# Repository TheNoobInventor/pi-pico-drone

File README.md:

# Raspberry pi pico drone

A micro drone is made using the Raspberry Pi Pico W. It is fitted with the MPU6050 IMU module and BMP280 barometric sensor. The drone will be controlled using TinyMPC and employ a Micro-ROS client on FreeRTOS.

🚧	***(Work in Progress)*** 

## Bill of Materials

The following components were used in this project:

| Part | Quantity |
| :-- | :-- |
| Raspberry Pi Pico W | 1 |
| MPU6050 module | 1 |
| BMP280 module | 1 |
| 1S 500mAh Lipo Battery| 1 |
| 1020 Coreless Motor | 4 |
| 66mm propeller (2 pairs of CW and 2 pairs of CCW) | 4  |
| XH2.54 2p connector pairs (for motors and battery) | 5 |
| si2302 N channel Mosfet| 4 |
| 1N4148 Diode | 5 |
| 100 ohm resistor | 3 |
| 300 ohm resistor | 1 |
| 1k ohm resistor | 1 |
| 10k ohm resistor | 4 |
| Female Pin headers | 40 |
| Push Button | 1 |
| LEDs | 3 |
| 1S Lipo charger | 1 |

*CW - Clockwise and CCW - Counter clockwise*

Some tools/parts used int he project are as follows:

| | Tool/Part |
| --| --|
|1| Soldering iron|
|2| 3D printer|
|3| Hot air gun|
|4| Crimping tool|
|4| Solder paste |

## Project Assembly and Wiring

The PCB was made with KiCAD and the project files are available in the [pcb directory](./hardware/pcb/).

The insides of one of the female headers had to be filed to enable the MPU6050 module be soldered and positioned horizontally to the pcb.

3D printed frame courtesy of this [thingiverse project](https://www.thingiverse.com/thing:4799075).

## Software installation
FreeRTOS
MicroROS
TinyMPC

TODO:
- Credit Anish Natekar's work
- Add component links
- Note on LED designations

# Acknowledgement
- [PicoW_Copter](https://github.com/anish-natekar/PicoW_Copter)
- [TinyMPC](https://github.com/TinyMPC/TinyMPC)

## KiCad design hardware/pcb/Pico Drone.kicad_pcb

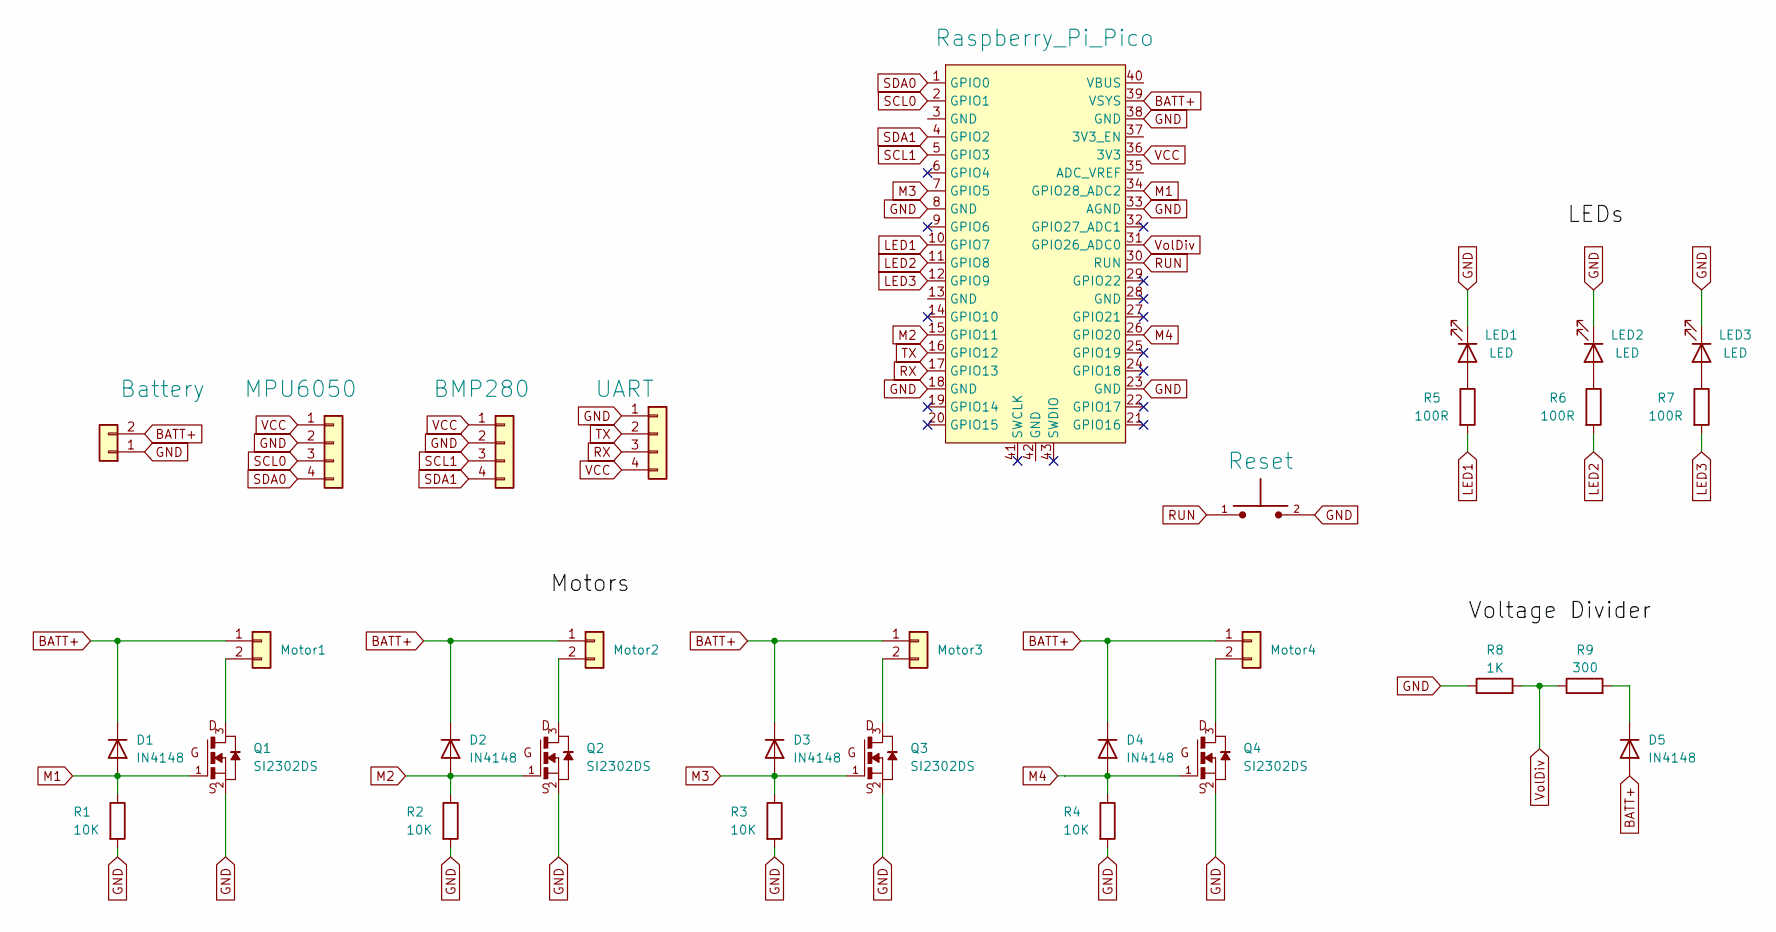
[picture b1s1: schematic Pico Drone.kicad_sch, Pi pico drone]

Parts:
Battery: Conn_01x02; PinHeader_1x02_P2.54mm_Vertical
D1, D2, D3, D4, D5: IN4148; Diode_DO-35
J1: MPU6050; PinHeader_1x04_P2.54mm_Vertical
J2: BMP280; PinHeader_1x04_P2.54mm_Vertical
J3: UART; PinHeader_1x04_P2.54mm_Vertical
LED1, LED2, LED3: LED; PinHeader_1x02_P2.54mm_Vertical
Motor1, Motor2, Motor3, Motor4: Conn_01x02; PinHeader_1x02_P2.54mm_Vertical
Q1, Q2, Q3, Q4: SI2302DS; SI2302
R1, R2, R3, R4: 10K; R_Axial_DIN0207_L6.3mm_D2.5mm_P7.62mm_Horizontal
R5, R6, R7: 100R; R_Axial_DIN0207_L6.3mm_D2.5mm_P7.62mm_Horizontal
R8: 1K; R_Axial_DIN0207_L6.3mm_D2.5mm_P7.62mm_Horizontal
R9: 300; R_Axial_DIN0207_L6.3mm_D2.5mm_P7.62mm_Horizontal
S1: Reset; smt_tactile_switch; PARTREV 1.0
U1: Raspberry_Pi_Pico

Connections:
BATT+: Battery.2, D1.1 (K), D2.1 (K), D3.1 (K), D4.1 (K), D5.2 (A), Motor1.1, Motor2.1, Motor3.1, Motor4.1, U1.39 (VSYS); also elsewhere on the board
GND: Battery.1, J1.2, J2.2, J3.1, LED1.1 (K), LED2.1 (K), LED3.1 (K), Q1.2, Q2.2, Q3.2, Q4.2, R1.2, R2.2, R3.2, R4.2, R8.1, S1.2, U1.8 (GND), U1.18 (GND), U1.23 (GND), U1.33 (AGND), U1.38 (GND); also elsewhere on the board
LED1: R5.2, U1.10 (GPIO7)
LED2: R6.2, U1.11 (GPIO8)
LED3: R7.2, U1.12 (GPIO9)
M1: D1.2 (A), Q1.1, R1.1, U1.34 (GPIO28_ADC2)
M2: D2.2 (A), Q2.1, R2.1, U1.15 (GPIO11)
M3: D3.2 (A), Q3.1, R3.1, U1.7 (GPIO5)
M4: D4.2 (A), Q4.1, R4.1, U1.26 (GPIO20)
unnamed: D5.1 (K), R9.2
unnamed: LED1.2 (A), R5.1
unnamed: LED2.2 (A), R6.1
unnamed: LED3.2 (A), R7.1
unnamed: Motor1.2, Q1.3
unnamed: Motor2.2, Q2.3
unnamed: Motor3.2, Q3.3
unnamed: Motor4.2, Q4.3
RUN: S1.1, U1.30 (RUN)
RX: J3.3, U1.17 (GPIO13)
SCL0: J1.3, U1.2 (GPIO1)
SCL1: J2.3, U1.5 (GPIO3)
SDA0: J1.4, U1.1 (GPIO0)
SDA1: J2.4, U1.4 (GPIO2)
TX: J3.2, U1.16 (GPIO12)
VCC: J1.1, J2.1, J3.4, U1.36 (3V3)
VolDiv: R8.2, R9.1, U1.31 (GPIO26_ADC0)

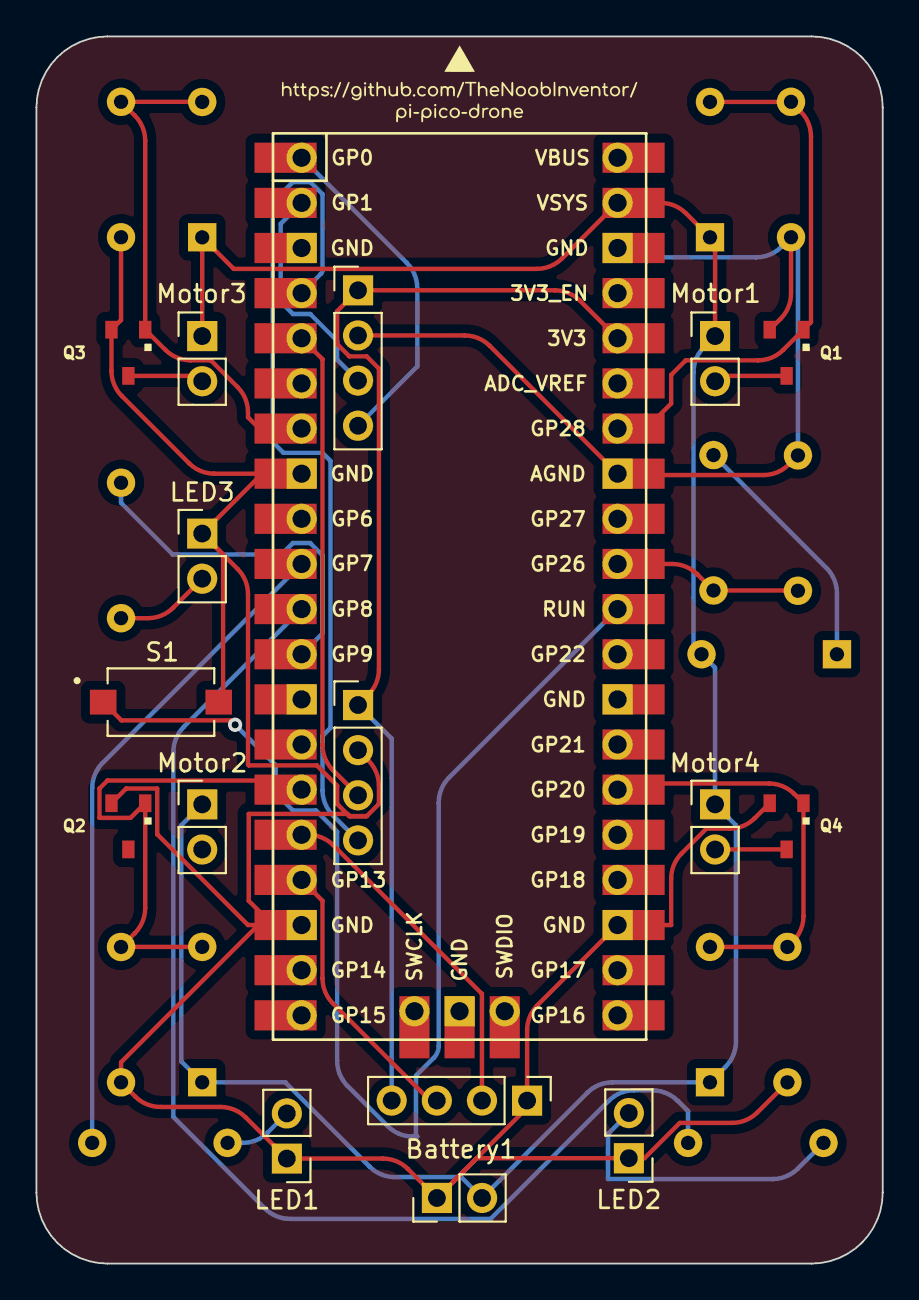
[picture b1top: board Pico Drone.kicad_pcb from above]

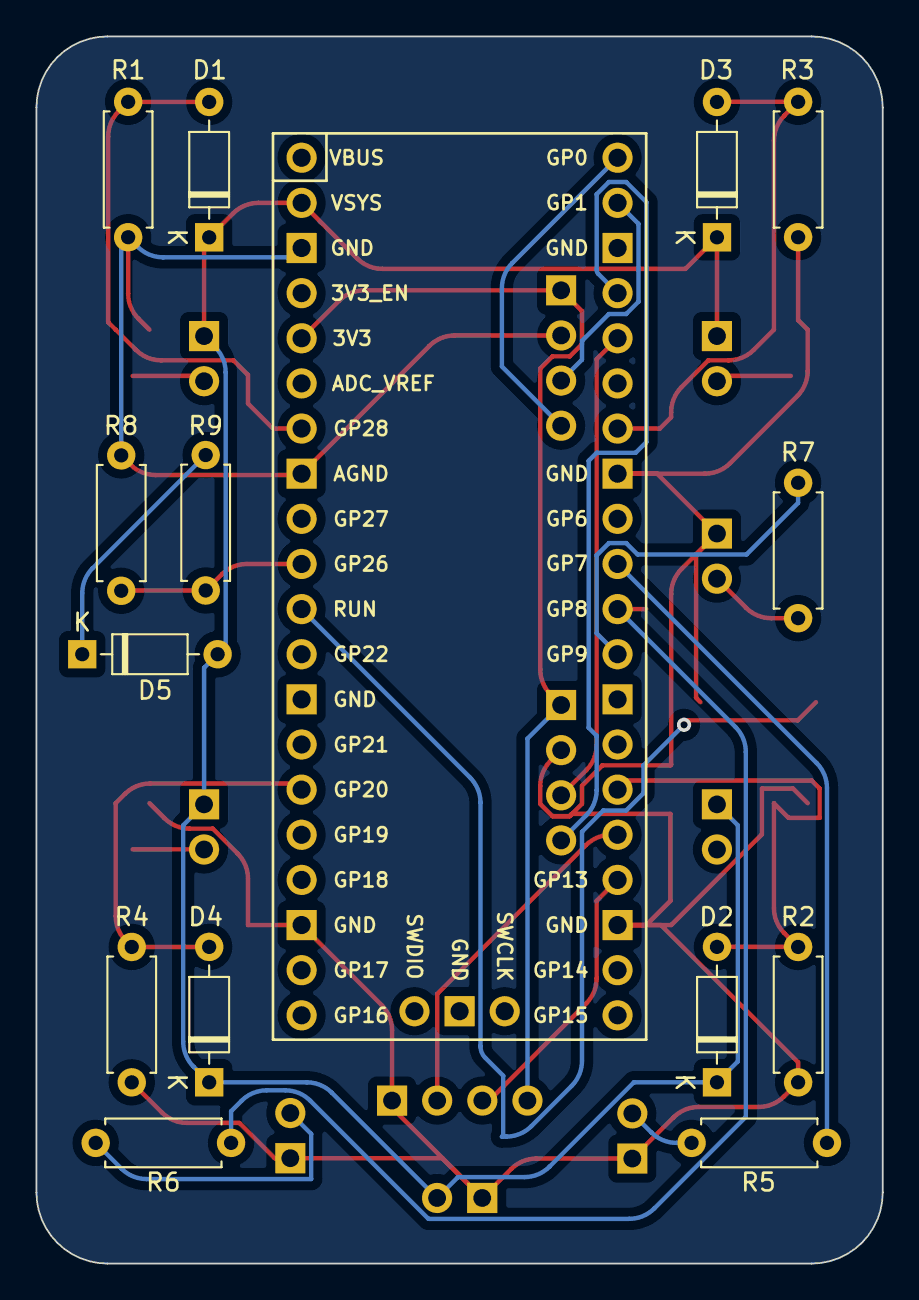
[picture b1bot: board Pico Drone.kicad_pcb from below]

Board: 2 copper layers, 47.6 x 69.1 mm, 31 parts (14 on the bottom side), 26 nets.

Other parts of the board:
Battery1: Conn_01x02; PinHeader_1x02_P2.54mm_Vertical

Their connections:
BATT+: Battery1.2; also elsewhere on the board
GND: Battery1.1; also elsewhere on the board

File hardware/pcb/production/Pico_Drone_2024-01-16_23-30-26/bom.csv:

Designator,Footprint,Quantity,Value,LCSC Part #
"Battery1, Motor1, Motor2, Motor3, Motor4",PinHeader_1x02_P2.54mm_Vertical,5,Conn_01x02,
"D1, D2, D3, D4, D5",Diode_DO-35,5,IN4148,
J1,PinHeader_1x04_P2.54mm_Vertical,1,MPU6050,
J2,PinHeader_1x04_P2.54mm_Vertical,1,BMP280,
J3,PinHeader_1x04_P2.54mm_Vertical,1,UART,
"LED1, LED2, LED3",PinHeader_1x02_P2.54mm_Vertical,3,LED,
"Q1, Q2, Q3, Q4",SI2302,4,SI2302DS,
"R1, R2, R3, R4",R_Axial_DIN0207_L6.3mm_D2.5mm_P7.62mm_Horizontal,4,10K,
"R5, R6, R7",R_Axial_DIN0207_L6.3mm_D2.5mm_P7.62mm_Horizontal,3,100R,
R8,R_Axial_DIN0207_L6.3mm_D2.5mm_P7.62mm_Horizontal,1,1K,
R9,R_Axial_DIN0207_L6.3mm_D2.5mm_P7.62mm_Horizontal,1,300,
Reset,smt_tactile_switch,1,switch,
U1,Raspberry_Pi_Pico,1,Raspberry_Pi_Pico,

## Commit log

2024-05-15 Add pcb and stl files, and update README
2026-05-02 Read data from MPU6050 module
